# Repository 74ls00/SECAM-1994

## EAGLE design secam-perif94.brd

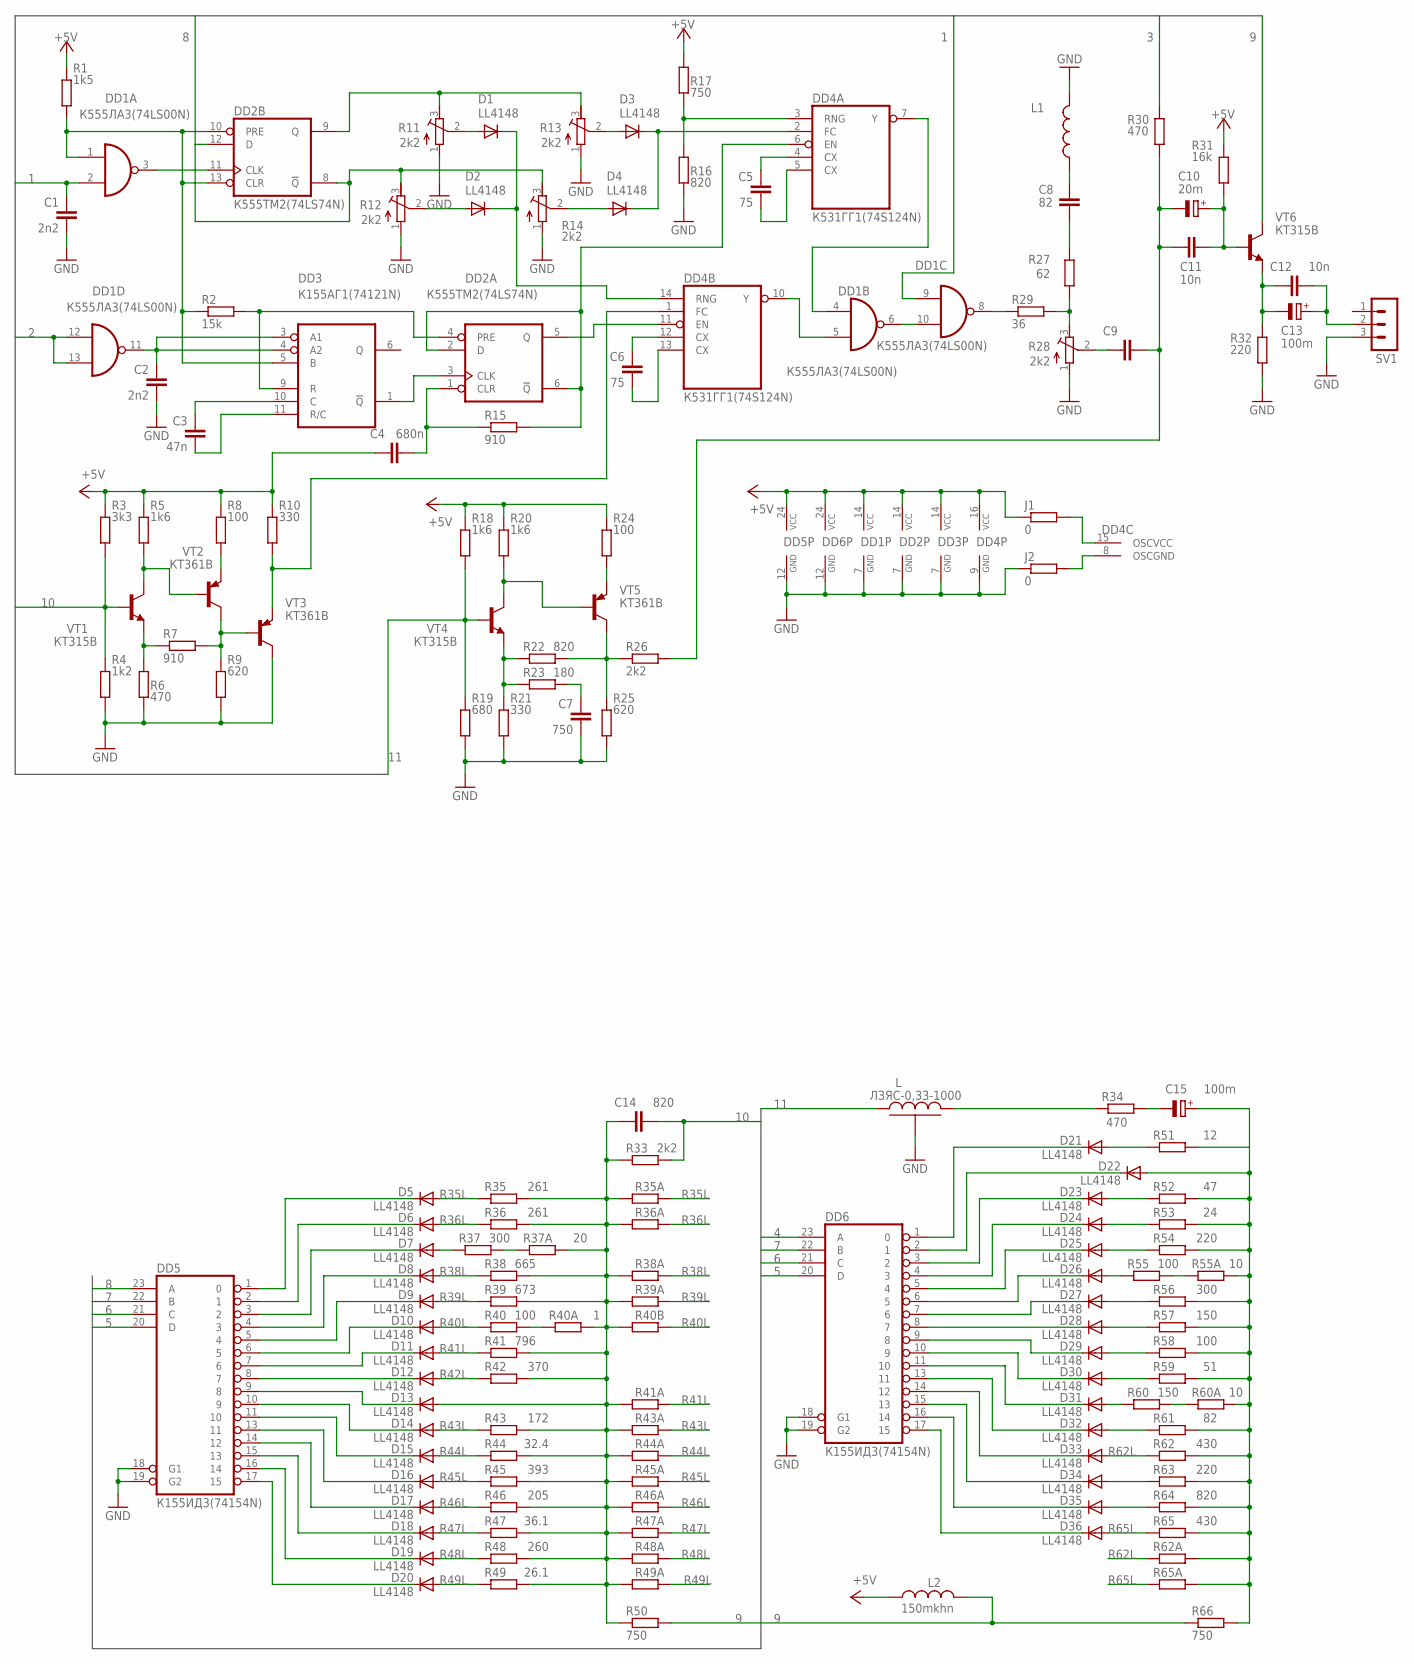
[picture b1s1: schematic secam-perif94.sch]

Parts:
C1, C2: 2n2; C025-025X050
C3: 47n; C025-025X050
C4: 680n; C025-025X050
C5, C6: 75; C025-025X050
C7: 750; C025-025X050
C8: 82; C025-025X050
C9: C-EU025-025X050; C025-025X050
C10: 20m; E2,5-5
C11, C12: 10n; C025-025X050
C13, C15: 100m; E2,5-5
C14: 820; C025-025X050
D1, D2, D3, D4, D5, D6, D7, D8, D9, D10, D11, D12, D13, D14, D15, D16, D17, D18, D19, D20, D21, D22, D23, D24, D25, D26, D27, D28, D29, D30, D31, D32, D33, D34, D35, D36: LL4148; SOD80C
DD1: К555ЛА3(74LS00N); DIL14
DD2: К555ТМ2(74LS74N); DIL14
DD3: К155АГ1(74121N); DIL14
DD4: К531ГГ1(74S124N); DIL16
DD5, DD6: К155ИД3(74154N); DIL24-6
J1, J2: 0; M0805
L: ЛЗЯС-0,33-1000
L1: L-US0204/7; 0204/7
L2: 150mkhn; 0207/15
R1: 1k5; M0805
R2: 15k; M0805
R3: 3k3; M0805
R4: 1k2; M0805
R5, R18, R20: 1k6; M0805
R6, R30, R34: 470; M0805
R7, R15: 910; M0805
R8, R24, R40, R55, R58: 100; M0805
R9, R25: 620; M0805
R10, R21: 330; M0805
R11, R12, R13, R14, R28: 2k2; RTRIM3296W
R16, R22, R64: 820; M0805
R17, R50, R66: 750; M0805
R19: 680; M0805
R23: 180; M0805
R26, R33: 2k2; M0805
R27: 62; M0805
R29: 36; M0805
R31: 16k; M0805
R32, R54, R63: 220; M0805
R35, R36: 261; M0805
R35A, R36A, R38A, R39A, R40B, R41A, R43A, R44A, R45A, R46A, R47A, R48A, R49A, R62A, R65A: R-EU_0207/10; 0207/10
R37, R56: 300; M0805
R37A: 20; M0805
R38: 665; M0805
R39: 673; M0805
R40A: 1; M0805
R41: 796; M0805
R42: 370; M0805
R43: 172; M0805
R44: 32.4; M0805
R45: 393; M0805
R46: 205; M0805
R47: 36.1; M0805
R48: 260; M0805
R49: 26.1; M0805
R51: 12; M0805
R52: 47; M0805
R53: 24; M0805
R55A, R60A: 10; M0805
R57, R60: 150; M0805
R59: 51; M0805
R61: 82; M0805
R62, R65: 430; M0805
SV1: MA03-1
VT1, VT4, VT6: КТ315В; TO92-ECB
VT2, VT3, VT5: КТ361В; TO92-BCE

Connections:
1: C1.1, DD1.2 (I1), DD1.9 (I0)
2: DD1.12 (I0), DD1.13 (I1)
3: R30.2
4: DD6.23 (A)
5: DD5.20 (D), DD6.20 (D)
6: DD5.21 (C), DD6.21 (C)
7: DD5.22 (B), DD6.22 (B)
8: DD2.8 (!Q), DD2.12 (D), DD5.23 (A), R12.3 (A), R14.3 (A)
9: L2.2, R50.2, R66.1, VT6.C
10: C14.2, R3.1, R4.2, R33.2, VT1.B
11: L.1, R18.1, R19.2, VT4.B
+5V: C4.1, DD1.14 (VCC), DD2.14 (VCC), DD3.14 (VCC), DD4.16 (VCC), DD5.24 (VCC), DD6.24 (VCC), J1.1, L2.1, R1.2, R3.2, R5.2, R8.2, R10.2, R17.2, R18.2, R20.2, R24.2, R31.2
GND: C1.2, C2.2, C7.2, DD1.7 (GND), DD2.7 (GND), DD3.7 (GND), DD4.9 (GND), DD5.12 (GND), DD5.18 (G1), DD5.19 (G2), DD6.12 (GND), DD6.18 (G1), DD6.19 (G2), J2.1, L.G, L1.2, R4.1, R6.1, R9.1, R11.1 (E), R12.1 (E), R13.1 (E), R14.1 (E), R16.1, R19.1, R21.1, R25.1, R28.1 (E), R32.1, SV1.3, VT3.C
unnamed: DD1.1 (I0), DD2.10 (PRE), DD2.13 (CLR), DD3.5 (B), R1.1, R2.1
unnamed: D7.C, DD5.3 (2)
unnamed: DD1.3 (O), DD2.11 (CLK)
unnamed: D6.C, DD5.2 (1)
unnamed: D11.C, DD5.7 (6)
unnamed: D10.C, DD5.6 (5)
unnamed: D9.C, DD5.5 (4)
unnamed: D8.C, DD5.4 (3)
unnamed: D5.C, DD5.1 (0)
unnamed: D12.C, DD5.8 (7)
unnamed: D13.C, DD5.9 (8)
unnamed: D14.C, DD5.10 (9)
unnamed: D15.C, DD5.11 (10)
unnamed: D16.C, DD5.13 (11)
unnamed: D17.C, DD5.14 (12)
unnamed: D18.C, DD5.15 (13)
unnamed: D19.C, DD5.16 (14)
unnamed: D20.C, DD5.17 (15)
unnamed: C15.-, R34.2
unnamed: DD2.9 (Q), R11.3 (A), R13.3 (A)
unnamed: D1.A, R11.2 (S)
unnamed: D2.A, R12.2 (S)
unnamed: DD1.8 (O), R29.1
unnamed: C14.1, D13.A, R33.1, R35.2, R35A.2, R36.2, R36A.2, R37A.2, R38.2, R38A.2, R39.2, R39A.2, R40A.2, R40B.2, R41.2, R41A.2, R42.2, R43.2, R43A.2, R44.2, R44A.2, R45.2, R45A.2, R46.2, R46A.2, R47.2, R47A.2, R48.2, R48A.2, R49.2, R49A.2, R50.1
unnamed: D3.A, R13.2 (S)
unnamed: D4.A, R14.2 (S)
unnamed: D7.A, R37.1
unnamed: D3.C, D4.C, DD4.2 (FC)
unnamed: C5.1, DD4.4 (CX)
unnamed: C5.2, DD4.5 (CX)
unnamed: DD4.3 (RNG), R16.2, R17.1
unnamed: DD2.2 (D), DD2.6 (!Q), DD4.6 (EN), R15.2
unnamed: C3.1, DD3.10 (C)
unnamed: C2.1, DD1.11 (O), DD3.3 (A1), DD3.4 (A2)
unnamed: C3.2, DD3.11 (R/C)
unnamed: DD2.4 (PRE), DD3.9 (R), R2.2
unnamed: DD2.5 (Q), DD4.11 (EN)
unnamed: DD2.3 (CLK), DD3.1 (!Q)
unnamed: C4.2, DD2.1 (CLR), R15.1
unnamed: D27.C, DD6.7 (6)
unnamed: D26.C, DD6.6 (5)
unnamed: D25.C, DD6.5 (4)
unnamed: D24.C, DD6.4 (3)
unnamed: D23.C, DD6.3 (2)
unnamed: D22.C, DD6.2 (1)
unnamed: D21.C, DD6.1 (0)
unnamed: D28.C, DD6.8 (7)
unnamed: D29.C, DD6.9 (8)
unnamed: D30.C, DD6.10 (9)
unnamed: D31.C, DD6.11 (10)
unnamed: D32.C, DD6.13 (11)
unnamed: D33.C, DD6.14 (12)
unnamed: D34.C, DD6.15 (13)
unnamed: D35.C, DD6.16 (14)
unnamed: D36.C, DD6.17 (15)
unnamed: R55.2, R55A.1
unnamed: D21.A, R51.1
unnamed: R37.2, R37A.1
unnamed: D1.C, D2.C, DD4.14 (RNG)
unnamed: D27.A, R56.1
unnamed: D28.A, R57.1
unnamed: D29.A, R58.1
unnamed: R60.2, R60A.1
unnamed: D30.A, R59.1
unnamed: D31.A, R60.1
unnamed: D32.A, R61.1
unnamed: C15.+, D22.A, R51.2, R52.2, R53.2, R54.2, R55A.2, R56.2, R57.2, R58.2, R59.2, R60A.2, R61.2, R62.2, R62A.2, R63.2, R64.2, R65.2, R65A.2, R66.2
unnamed: D34.A, R63.1
unnamed: D35.A, R64.1
unnamed: C6.1, DD4.12 (CX)
unnamed: C6.2, DD4.13 (CX)
unnamed: L.2, R34.1
unnamed: DD1.4 (I0), DD4.7 (Y)
unnamed: DD1.5 (I1), DD4.10 (Y)
unnamed: D26.A, R55.1
unnamed: D25.A, R54.1
unnamed: D24.A, R53.1
unnamed: D23.A, R52.1
unnamed: DD1.6 (O), DD1.10 (I1)
unnamed: R27.1, R28.3 (A), R29.2
unnamed: C9.1, R28.2 (S)
unnamed: C8.1, R27.2
unnamed: C8.2, L1.1
unnamed: R5.1, VT1.C, VT2.B
unnamed: C10.+, C11.2, R31.1, VT6.B
unnamed: C12.1, C13.-, R32.2, VT6.E
unnamed: C12.2, C13.+, SV1.2
unnamed: C9.2, C10.-, C11.1, R26.2, R30.1
unnamed: R6.2, R7.1, VT1.E
unnamed: R7.2, R9.2, VT2.C, VT3.B
unnamed: R8.1, VT2.E
unnamed: DD4.1 (FC), R10.1, VT3.E
unnamed: R20.1, VT4.C, VT5.B
unnamed: R21.2, R22.1, R23.1, VT4.E
unnamed: DD4.8 (OSCGND), J2.2
unnamed: DD4.15 (OSCVCC), J1.2
unnamed: C7.1, R23.2
unnamed: R22.2, R25.2, R26.1, VT5.C
unnamed: R24.1, VT5.E
R35L: D5.A, R35.1, R35A.1
R36L: D6.A, R36.1, R36A.1
R38L: D8.A, R38.1, R38A.1
R39L: D9.A, R39.1, R39A.1
R40L: D10.A, R40.1, R40B.1
R40O: R40.2, R40A.1
R41L: D11.A, R41.1, R41A.1
R42L: D12.A, R42.1
R43L: D14.A, R43.1, R43A.1
R44L: D15.A, R44.1, R44A.1
R45L: D16.A, R45.1, R45A.1
R46L: D17.A, R46.1, R46A.1
R47L: D18.A, R47.1, R47A.1
R48L: D19.A, R48.1, R48A.1
R49L: D20.A, R49.1, R49A.1
R62L: D33.A, R62.1, R62A.1
R65L: D36.A, R65.1, R65A.1

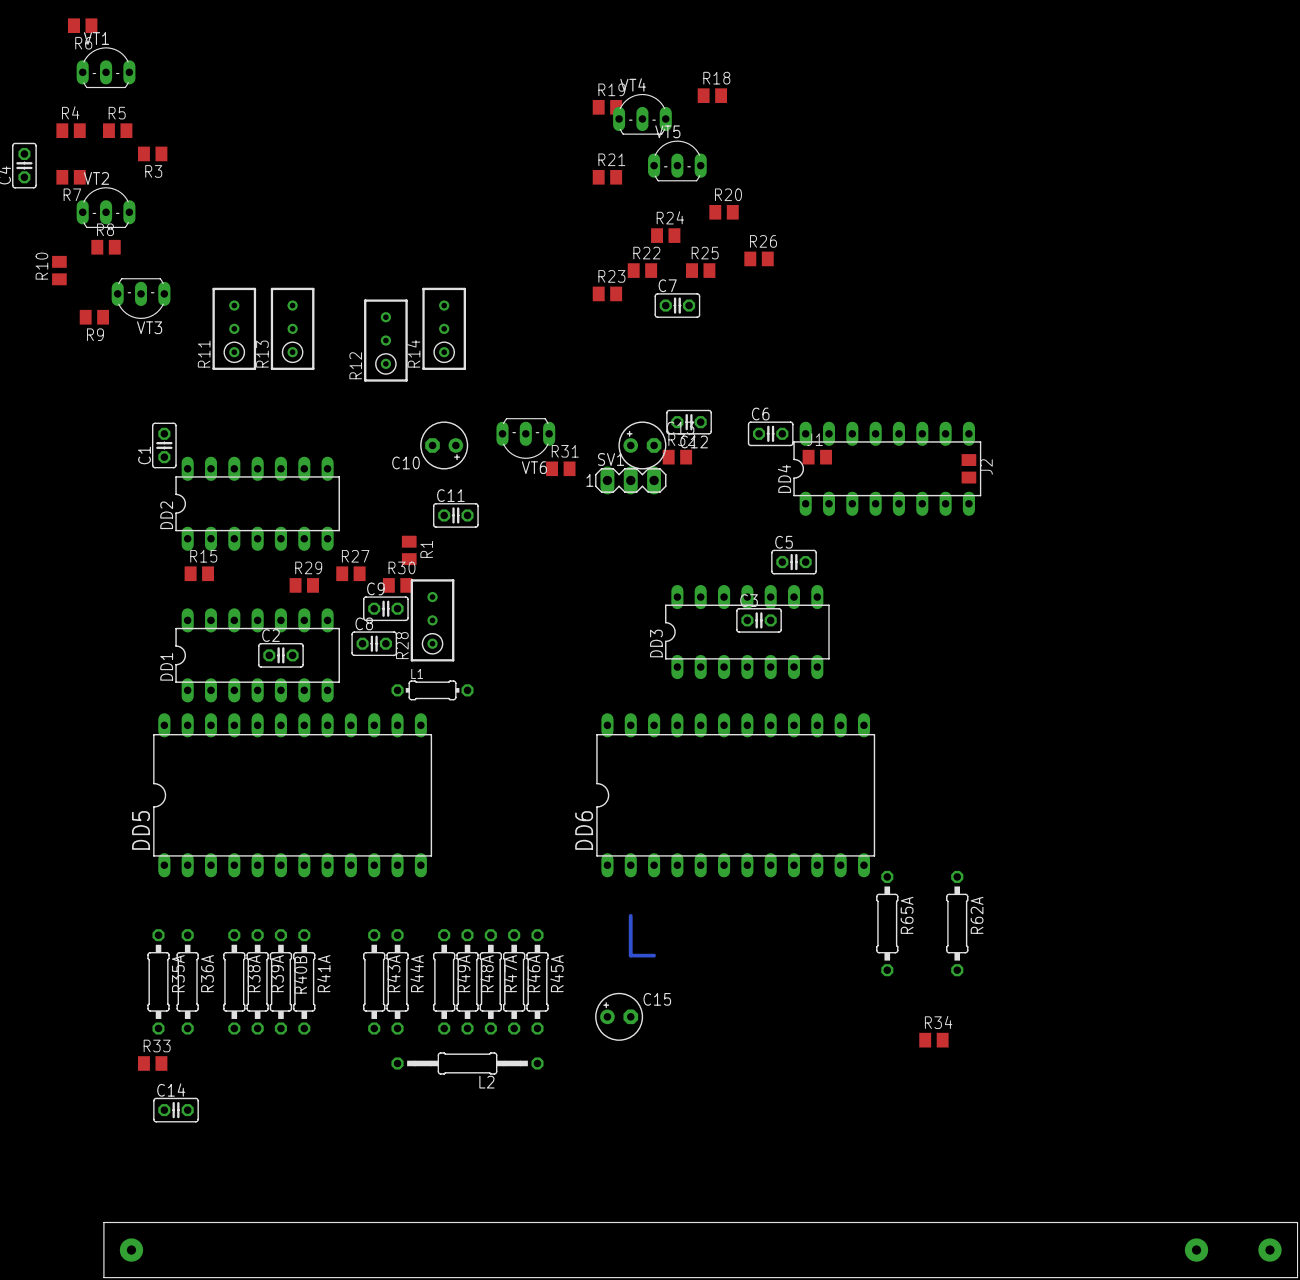
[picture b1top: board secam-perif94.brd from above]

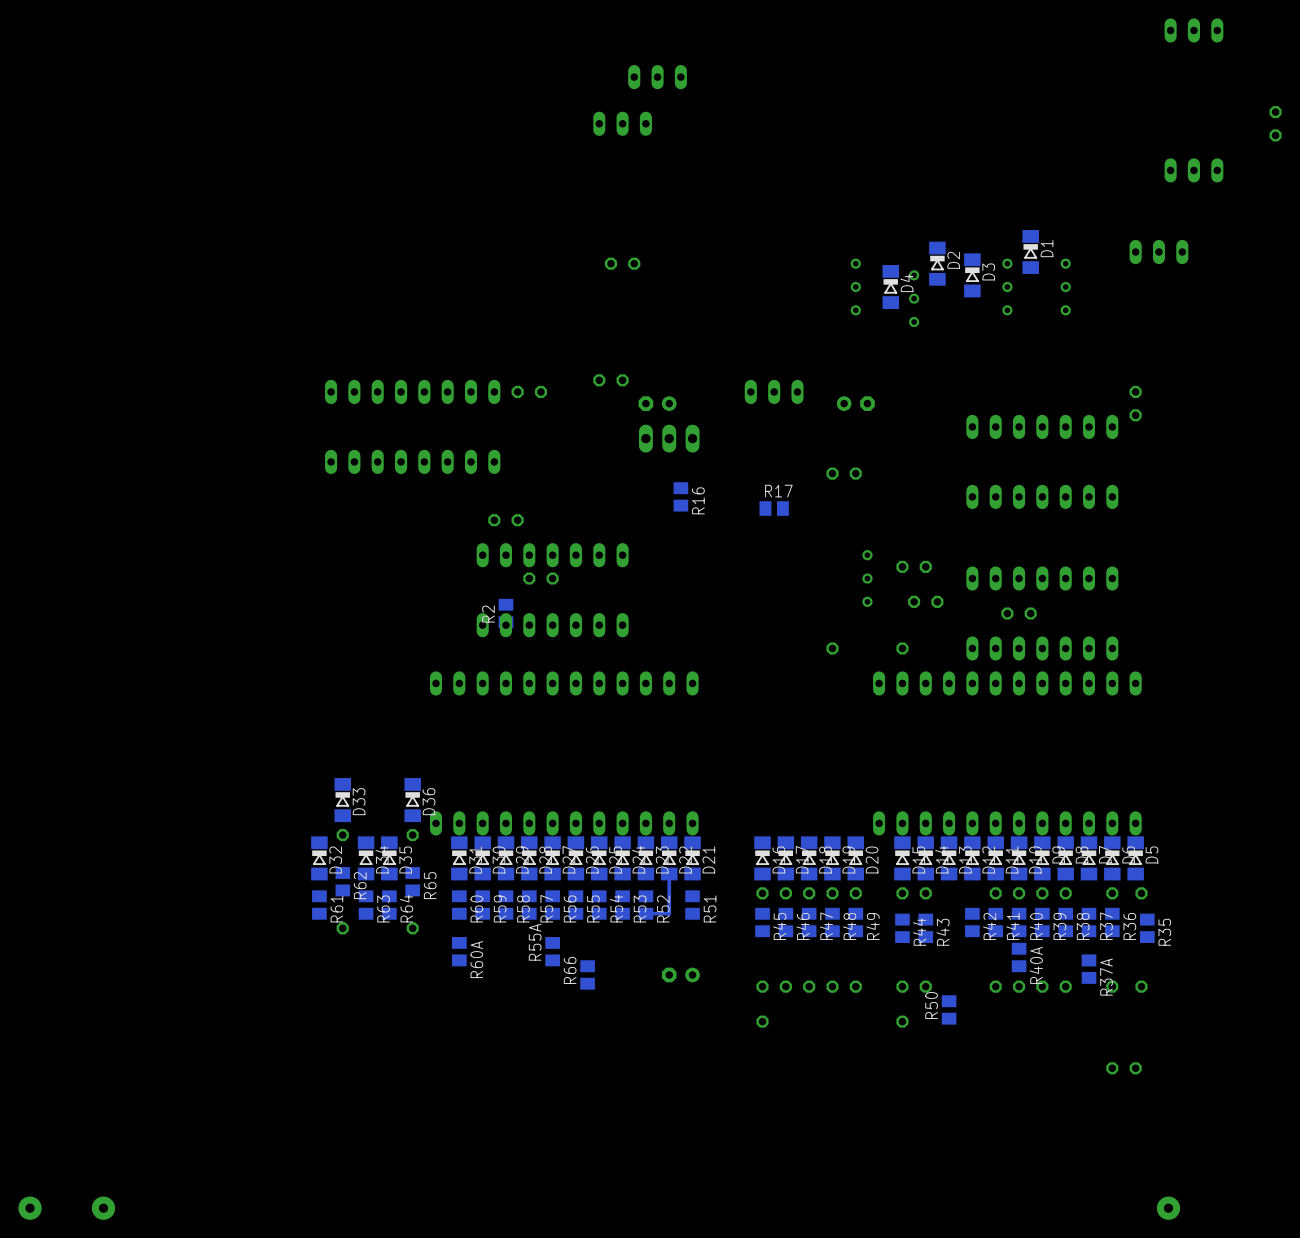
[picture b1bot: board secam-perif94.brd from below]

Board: 2 copper layers, 154 parts (75 on the bottom side), 127 nets.
